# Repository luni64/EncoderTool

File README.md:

# EncoderTool  [![Badge License]][License]  [![Badge Arduino]][Arduino]  [![Badge PlatformIO]][PlatformIO]

*Bounce-Free Rotary Encoder Library* <br>
 **+** *Standard or Multiplexed Wiring* <br>
 **+** *Push Button Support* <br>
 **+** *Callback System*

<br>

<div align = center>

---

[<kbd> <br> Examples <br> </kbd>][Examples] 
[<kbd> <br> Boards <br> </kbd>][Schematics] 
[<kbd> <br> Documentation <br> </kbd>][Documentation] 
[<kbd> <br> Contributors <br> </kbd>][Contributors]

---
</div>

<br>

## Supports

<br>

- All common encoders with and without push buttons

- Directly connected encoders (A+B+Button to pins)

- Multiplexed encoders using

    - [`74HC165 (up to 32 encoders)`][MPLEX74165]

    - [`40HC67  (up to 16 encoders)`][MPLEX4067]

    - [`40HC51  (up to 8 encoders)`][MPLEX4051]
    
    - [`Encoder Matrix`][MPLEX_Matrix]

    - Easy to adapt for your preferred multiplexer

- Interrupt based or polled readout strategies

<br>

## Board Compatibility

<br>

- PJRC Teensy (Teensy-LC, Teensy 3.x, Teensy 4.x, MicroMod)

- SAMD (SEEED XIAO, Nano33 ...)

- 8bit Arduino AVR (UNO, Nano, Mega...)

- ESP32

- Fallback solution for other boards (using slow digitalRead/Write)

<br>

## Features

- Fully bounce free readout without additional hardware

- Provides hard and cyclic count limits

- Supports and debounces encoder push buttons

- Modern callback system for event driven applications

- Encoders can be connected directly (A / B / Btn connected to pins)

- Encoder connection using various multiplexers (up to 32 encoders on only 4 control pins)

- Schematics and Gerbers available for multiplexed encoder boards (Eagle/KiCad).

<!----------------------------------------------------------------------------->

[PlatformIO]: https://registry.platformio.org/libraries/luni64/EncoderTool/
[Arduino]: https://www.arduino.cc/reference/en/libraries/encodertool/

[License]: LICENSE
[MPLEX74165]:Resources/Extras#multiplexing-with-74hc165
[MPLEX4067]:Resources/Extras#multiplexing-with-cd4067
[MPLEX4051]:Resources/Extras#multiplexing-with-cd4051
[MPLEX_Matrix]:Resources/Extras#using-a-directly-connected-encoder-matrix

[Documentation]: Documentation/Overview.md
[Contributors]: Documentation/Contributors.md
[Schematics]: Resources/Extras
[Examples]: examples

[MPLEX74165]: Resources/Extras/Boards/MPX_74165
[MPLEX4067]: Resources/Extras/Boards/MPX_4067
[MPLEX4051]: Resources/Extras/Boards/MPX_4051

<!--------------------------------{ Badges }----------------------------------->

[Badge PlatformIO]: https://img.shields.io/badge/PlatformIO-EncoderTool-fd7e14.svg?style=for-the-badge
[Badge Arduino]: https://img.shields.io/badge/EncoderTool-00979D.svg?style=for-the-badge&logo=Arduino&logoColor=white&labelColor=gray
[Badge License]: https://img.shields.io/badge/License-MIT-yellow.svg?style=for-the-badge

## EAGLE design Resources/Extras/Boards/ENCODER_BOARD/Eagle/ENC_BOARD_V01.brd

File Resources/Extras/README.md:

# Test Boards

This folder contains proposals and information how to use a 74HC165 shift register or the CD74HC4062 to multiplex rotary encoders. It also contains and a small encoder test board for up to 8 encoders.

<!-- vscode-markdown-toc -->
* [Encoder Board](#EncoderBoard)
* [Multiplexing with 74HC165](#Multiplexerwith74HC165)
* [Multiplexing with CD74HC4067](#MultiplexerwithCD74HC4067)
* [Multiplexing with CD74HC4051](#MultiplexerwithCD74HC4051)
* [Using a directly connected Encoder Matrix](#EncoderMatrix)

<!-- vscode-markdown-toc-config
	numbering=false
	autoSave=true
	/vscode-markdown-toc-config -->
<!-- /vscode-markdown-toc -->

## Encoder Board

Test board for 8 encoders with or without pushbuttons. The layout is done for the common 5mm [footprint](Boards/ENCODER_BOARD/footprint.jpg).

Overview:

- Schematic: [ENC_BOARD_V0.1.pdf](Boards/ENCODER_BOARD/Schematic.pdf)
- Gerbers: [CAMOutputs.zip](Boards/ENCODER_BOARD/Eagle/CAMOutputs.zip)

- BOM: https://octopart.com/bom-tool/XXf3nZh4

Assembly:\

Dimensions:\

## Multiplexing with 74HC165

Multiplexer for 8 encoders with or without additional pushbuttons using two (three) [74HC165](https://octopart.com/search?currency=USD&oq=74HC165+shift&q=74HC165+shift+register&specs=1&case_package=PDIP&case_package=DIP&rohs=Compliant) shift registers.

The following schematic shows the circuit idea. The two phases A and B of up to 8 encoders are connected to the inputs A-H of the first two shift registers. The optional pushbuttons are connected to the inputs of the third shift register.
The controller will use the common clock and load signals to read in the encoders  one after the other. For each encoder it calculates the new encoder count based on the old and the new phases A/B and pushbutton state S. The full schematic of the test board can be found [here](Boards/MPX_74165/MPX_74165_Schematic.pdf).

The board can be daisy chained if you need more than 8 encoders.

### Please note:
The 74HC165 shifts the encoders in from H to A. Thus, if you have less than 8 encoders connect them to H,G...  instead of A,B...

Board:\

Assembly:\

Dimensions:\

- Schematic: [MPX_74165_Schematic.pdf](Boards/MPX_74165/MPX_74165_Schematic.pdf)
- Gerbers: [CAMOutputs.zip](Boards/MPX_74165/Eagle/CAMOutputs.zip)
- BOM: https://octopart.com/bom-tool/vhNEkctc

## Multiplexing with CD4067

The [CD4067](http://www.ti.com/product/CD4067B) is a wide spread and easy to use 16 channel analog/digital multiplexer. Depending on the channel address which has to be supplied at the pins S0-S4, the multiplexer connects one of the 16 inputs C0-C15 to the common output SIG.
To multiplex rotary encoders we use two of the chips, one for the encoder phases A and one for phases B. If you want to use additional pushbuttons you can connect them to an additional multiplexer.

If you don't want to design a dedicated PCB, CD4067 breakout boards are readily available e.g. at SparkFun https://www.sparkfun.com/products/9056.

\
([CC BY 2.0](https://creativecommons.org/licenses/by/2.0/) SparkFun)

The schematic below shows the principle (not all encoders drawn). The pin names are chosen to match the print on the breakout boards.

If you use the breakout boards they can be assembled in the very compact way shown in the drawing below.

![Breakout](Boards/MPX_4067/assembly3d.jpg
)

Extending the assembly to a third board to connect the encoder pushbuttons is straight forward.

## Multiplexing with CD4051

The [CD4051](http://www.ti.com/product/CD4051B) is an 8 channel analog/digital multiplexer, available in through-hole and SMD packages. Depending on the channel address which has to be supplied at the pins S0-S2, the multiplexer connects one of the 8 inputs to the common output.

To multiplex rotary encoders we use two of the chips, one for the encoder phases A and one for phases B. If you want to use additional pushbuttons you can connect them to an additional multiplexer.

The recommended through-hole component is the CD74HC4051. There's an older CD4051B available, but it is too slow to accurately read multiple encoders without significantly slowing down the scanning speed.

The schematic below shows how to connect your encoders and multiplexers ([full PDF](Boards/MPX_4051/MPX_4051_Schematic.pdf)). 3.3V from the Teensy is used to supply VCC.

## Using a directly connected Encoder Matrix

Instead of using external multiplexers one can use a Teensy to read out\
a matrix of encoders.

Here a schematic and 3d views of a corresponding prototype board
([full PDF](Boards/MATRIX/documentation/schematic.pdf)).\
The controller sets one column pin at a time to HIGH and queries\
the A/B/S pins of the individual rows.

The board can be used for prototypes as well as finished products.\
To accommodate the final, mechanical setup the rows and columns\
can be broken apart. Wiring of the singled encoder boards is easy using\
the provided pads. The layout of the board allows to use a Teensy or\
similar board as controller.

Front

Back

Production files (gerbers, drill files) can be found in the extras folder.

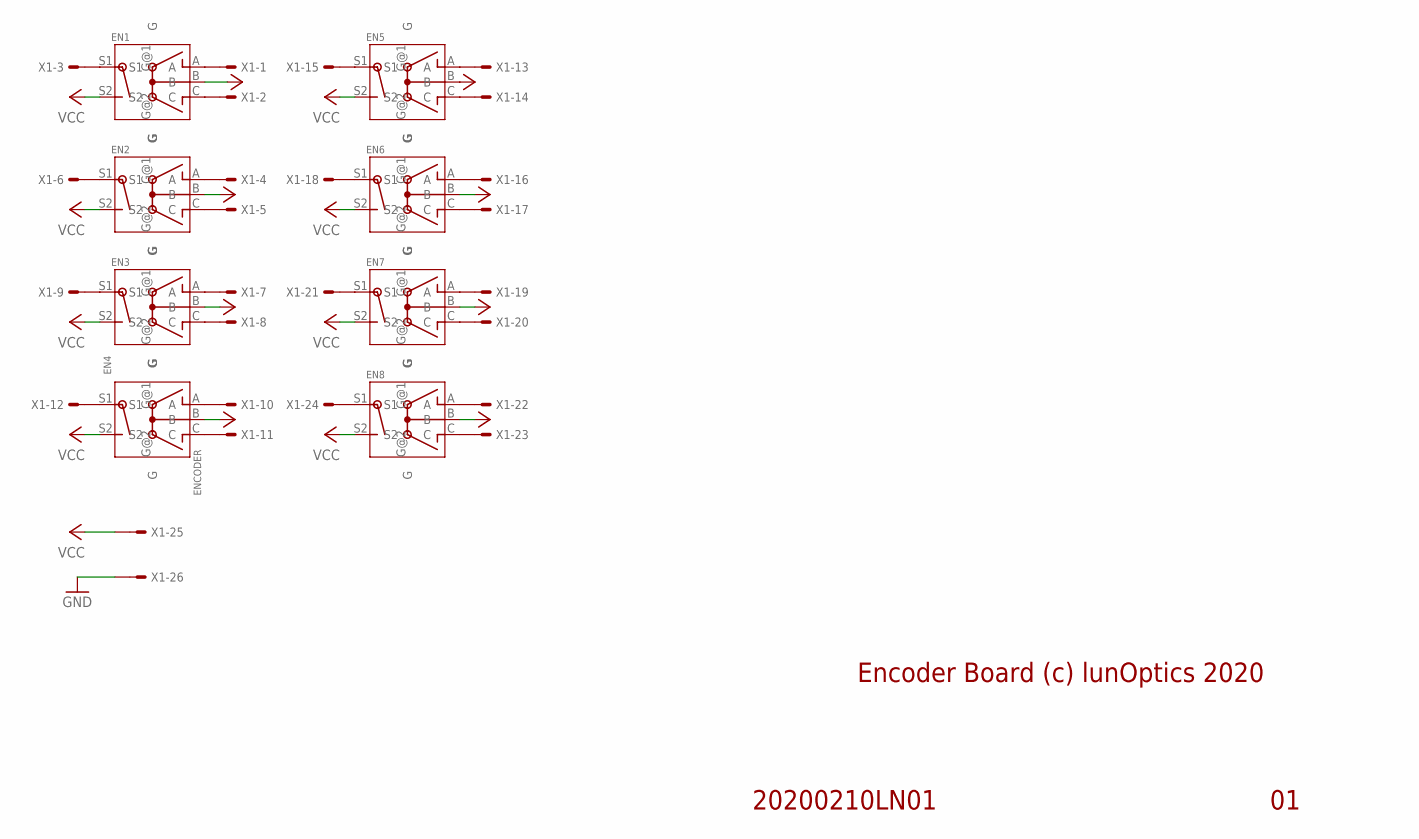
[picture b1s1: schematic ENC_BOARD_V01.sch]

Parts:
EN1, EN2, EN3, EN4, EN5, EN6, EN7, EN8: ENCODER
X1: 057-026-1

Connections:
GND: X1.26
unnamed: EN1.A, X1.1
unnamed: EN1.C, X1.2
unnamed: EN1.S1, X1.3
unnamed: EN2.A, X1.4
unnamed: EN2.C, X1.5
unnamed: EN2.S1, X1.6
unnamed: EN3.A, X1.7
unnamed: EN3.C, X1.8
unnamed: EN3.S1, X1.9
unnamed: EN4.A, X1.10
unnamed: EN4.C, X1.11
unnamed: EN4.S1, X1.12
unnamed: EN5.A, X1.13
unnamed: EN5.C, X1.14
unnamed: EN5.S1, X1.15
unnamed: EN6.A, X1.16
unnamed: EN6.C, X1.17
unnamed: EN6.S1, X1.18
unnamed: EN7.A, X1.19
unnamed: EN7.C, X1.20
unnamed: EN7.S1, X1.21
unnamed: EN8.A, X1.22
unnamed: EN8.C, X1.23
unnamed: EN8.S1, X1.24
VCC: EN1.B, EN1.S2, EN2.B, EN2.S2, EN3.B, EN3.S2, EN4.B, EN4.S2, EN5.B, EN5.S2, EN6.B, EN6.S2, EN7.B, EN7.S2, EN8.B, EN8.S2, X1.25

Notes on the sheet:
Encoder Board (c) lunOptics 2020
20200210LN01

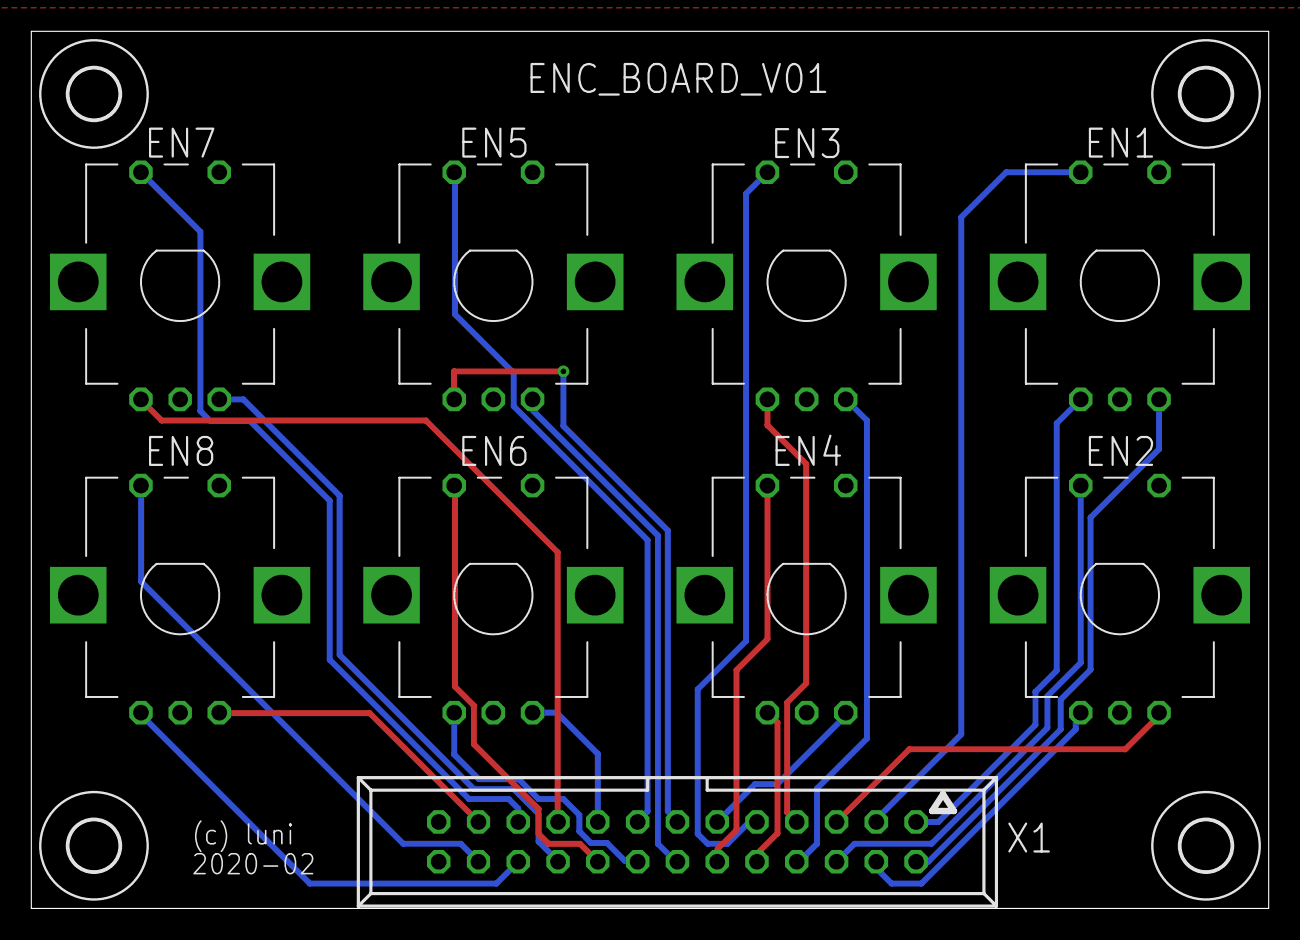
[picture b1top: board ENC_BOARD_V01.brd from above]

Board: 2 copper layers, 79.0 x 56.0 mm, 13 parts (0 on the bottom side), 25 nets.

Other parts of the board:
U$1, U$2, U$3, U$4: 3,2

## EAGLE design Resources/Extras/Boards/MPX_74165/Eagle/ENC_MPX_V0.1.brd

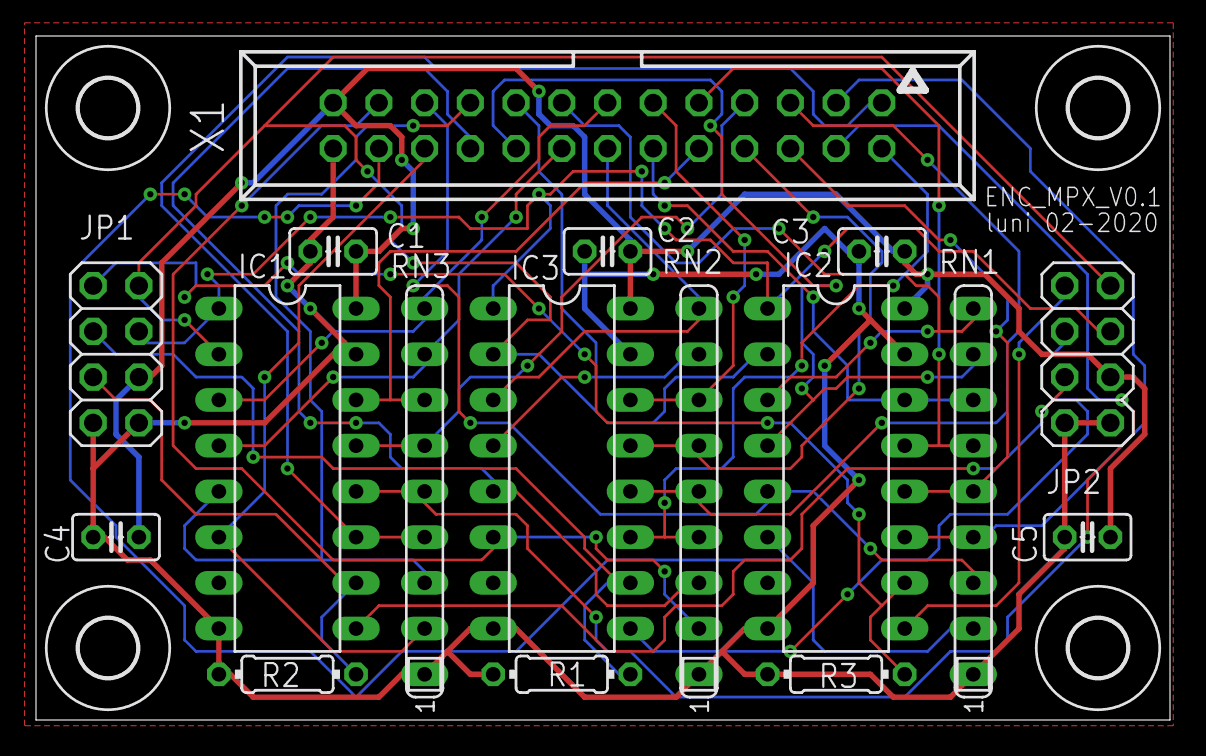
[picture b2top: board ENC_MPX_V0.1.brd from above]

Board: 2 copper layers, 63.0 x 38.0 mm, 21 parts (0 on the bottom side), 34 nets.

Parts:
C1, C2, C3, C4, C5: 100n; C025-025X050
IC1, IC2, IC3: 74HC165N; DIL16
JP1, JP2: 2X04
R1, R2, R3: 4k7; 0204/7
RN1, RN2, RN3: 4k7; SIL9
U$1, U$2, U$3, U$4: 3,2
X1: 057-026-1

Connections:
!LD: IC1.1, IC2.1, IC3.1, JP1.4, JP2.4
A1: IC1.11, RN3.4, X1.1
A2: IC1.12, RN3.5, X1.4
A3: IC1.13, RN3.6, X1.7
A4: IC1.14, RN3.7, X1.10
A5: IC1.3, RN3.9, X1.13
A6: IC1.4, RN3.8, X1.16
A7: IC1.5, RN3.3, X1.19
A8: IC1.6, RN3.2, X1.22
B1: IC3.11, RN2.4, X1.2
B2: IC3.12, RN2.5, X1.5
B3: IC3.13, RN2.6, X1.8
B4: IC3.14, RN2.7, X1.11
B5: IC3.3, RN2.9, X1.14
B6: IC3.4, RN2.8, X1.17
B7: IC3.5, RN2.3, X1.20
B8: IC3.6, RN2.2, X1.23
CLK: IC1.2, IC2.2, IC3.2, JP1.2, JP2.2
GND: C1.2, C2.2, C3.2, C4.2, C5.2, IC1.8, IC1.15, IC2.8, IC2.15, IC3.8, IC3.15, JP1.7, JP1.8, JP2.7, JP2.8, R1.1, R2.2, R3.1, RN1.1, RN2.1, RN3.1, X1.26
QA: IC1.9, JP2.5
QB: IC3.9, JP2.3
QS: IC2.9, JP2.1
S1: IC2.11, RN1.4, X1.3
S2: IC2.12, RN1.5, X1.6
S3: IC2.13, RN1.6, X1.9
S4: IC2.14, RN1.7, X1.12
S5: IC2.3, RN1.9, X1.15
S6: IC2.4, RN1.8, X1.18
S7: IC2.5, RN1.3, X1.21
S8: IC2.6, RN1.2, X1.24
SER_A: IC1.10, JP1.5, R2.1
SER_B: IC3.10, JP1.3, R1.2
SER_S: IC2.10, JP1.1, R3.2
VCC: C1.1, C2.1, C3.1, C4.1, C5.1, IC1.16, IC2.16, IC3.16, JP1.6, JP2.6, X1.25

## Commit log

2020-08-28 updated examples and removed throw_bad_function which is not needed anymore
2020-08-28 Rename setACallback -> attachCallback
2020-08-28 Updated examples
2020-08-28 cleanup
2020-08-29 Bump versions
2020-08-31 Moved count mode to begin instead of constructor
2020-08-31 Added interrupt based single encoder as standard. The polled encoder moved to PolledEncoder class
2020-08-31 Changed the 'all encoders callback' to include delta information to by symmetric to the single encoder callbacks
2020-08-31 Bump version to v2.0.0
2020-09-06 Changed attachInterruptEx to use a more flexible method to generate the relay function array
2020-09-06 cleanup structure
2020-09-06 added button handling in polled and multiplexed encoders
2020-09-06 Encoder button example
2020-09-06 Bump Version
2020-10-04 fixed bug in plain vanilla callbacks
2020-10-04 Switch from std::function to void(*)(Encoder*) for the attached pin interrupts. Reason: avoid a large memory footprint for small MCUs like T-LC
2020-12-02 Update 03_Multiplexed_4067.ino
    Improved call frequency of encoders.tick by eliminating the delay in loop
2020-12-21 workaround std::function issue if _write is not defined. This happens if the linker doesn't link in the print class. Provides a dummy definition for _write
2020-12-23 Fixed wrong conditional code
2020-12-25 Added missing inline declaration
2021-03-07 Added metronome example
2021-03-07 fixed file extension
2021-11-22 Clarified connection of encoders to the 74165 multiplexers
2022-02-10 Add a new class for 4051 multiplexers
    Based on the `EncPlex4067` class, but with three address selector pins instead of 4 and a maximum of 8 encoders.
2022-02-10 Add an example sketch for the 4051
2022-02-10 Add a schematic and documentation for the 4051 multiplexer
2022-02-10 Add 4051 to the readme
2022-02-11 Added 4051 to the TOC
2022-04-24 Fix std::function / printf workaround
    There is a linking issue in Teensyduino which prevents linking in the weak _write function in certain circumstances. The EncoderTool provides a copy of the _write function to avoid this issue.
2022-05-04 Formatted Features
2022-05-04 Added Quicklinks
2022-05-04 Added License Badge
2022-05-04 Added PlatformIO Badge
2022-05-04 Adjusted Style
2022-05-04 Fixed Typo
2022-05-04 Prepare platform independence
2022-05-04 Change digitalWriteFast to HAL::direct read / write
2022-05-04 Prepare platform independent pin interrupts
2022-05-04 Added ESP32 to direct read/write
2022-05-04 Readme experiments
2022-05-04 Copied Over Wiki
2022-05-04 Sorted Files
2022-05-04 Sorted Out Overview
2022-05-04 Updated Links
2022-05-04 Basic Installation Instructions
2022-05-04 Renamed File
2022-05-05 updated badges
2022-05-05 restructured detection of used cores
2022-05-07 Sorted Images
2022-05-07 Formatted Connecting Encoders
2022-05-07 Improve HAL
2022-05-07 Adapted Encoder classes to new HAL
2022-05-07 Formatted Limits
2022-05-08 other readme experiments
2022-05-08 Formatted Interrupts Vs Polling
2022-05-08 Tidied Up Names
2022-05-08 Restructured examples
2022-05-08 Changed encoder values from int32_t to int. -> 16bit for 8bit AVRs, 32bit for ARM processors
2022-05-08 Added the simplyAtomic library to get platform independent ATOMIC blocks.
    Most of the platforms provide atomic ways to set/reset digital pins. For AVR boards this needs to be protected with an atomic block. Same for returning the 16bit counter value
2022-05-08 experiments, to style the readme. Looks like github is removing any css code from the README
2022-05-09 Integrated SimplyAtomic to the repo since platformIO had a hard time autoinstalling it
2022-05-10 fixed dependency bug in library.properties
2022-05-11 Formatted Bouncing
2022-05-11 Added Banners
2022-05-11 Formatted Overview
2022-05-11 Added Button Colors
2022-05-11 Adjusted Spacing
2022-05-11 Fixed Arduino FileSystem
2022-05-11 Formatted Types
2022-05-11 Formatted Guide
2022-05-11 Updated landing page to current state
2022-05-12 Updated Banner
2022-05-12 Formatted Detents
2022-05-12 Fixed Link
2022-05-12 Formatted Reference
2022-05-12 Basic README Fixup
2022-05-13 Added Contributors Page
2022-05-13 Adjusted Filename
2022-05-13 Fixed quick-links formatting
2022-05-15 Squashed commit of the following:
    commit 65bf7239800057a17565193f4fc4afeecebc231b
    Author: luni64 <12611497+luni64@users.noreply.github.com>
    Date: Sun May 15 15:08:58 2022 +0200
    Added MCP23S17 multiplexer example
2022-05-23 Added encoder-matrix board
2022-05-23 Encoder Matrix documentation
2022-05-25 Fixed some platform dependencies in the examples
2022-07-11 Fix directRead for T_LC
2022-07-20 fixed inlining bug preventing linking if lib is included from different translational units
2022-07-20 bump version to v3.03
2022-07-22 Fix directWrite for T_LC
2022-07-22 Bump version to v3.0.5
2022-08-09 matrix example added
2022-08-09 Fixed errors in matrix test board
2022-08-09 bump version to 3.0.6
2022-10-16 User selectable type of the encoder counter
2022-10-17 moved callback typedefs from config.h to base classes to reflect counter type
2022-10-17 Cleaned up API, removed callback from begin function (use attachCallback instead)
2022-10-18 fix wrong type of channel
2022-10-18 Compatibility to 8bit AVR boards (Uno...)
2022-11-29 Merged StaticFunctional, WIP
2022-11-29 Replaced StaticFunctional by the c++ proposed stdext::inplace_function
2022-11-29 Use modern callbacks by default
2022-12-01 Compatibility to c++11 toolchains (WIP)
2022-12-18 Fix examples
2022-12-18 added unit and compile tests
2022-12-18 adapt gitignore to pio project
2023-01-27 Fix namespace issue when using together with TimerTool
2023-02-10 feat: Add button callback to multiplexed
2023-05-24 fix compile issue with non-Teensy boards
2023-10-06 Fixed typo and link to schematic
2023-11-11 Rename to avoid confusion
    This has to be reverted before pullRequest
2023-11-12 isolate update function for btn
2023-11-12 finish allBtnCallback func template
2023-11-12 replicate encoderCallback for button
2023-11-12 Reverted alt dev naming
2024-04-19 Fix wrong startup pin pattern after power on
2025-01-15 first test
2025-08-02 Make error callback work
    ...and enable it
